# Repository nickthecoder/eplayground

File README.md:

Modular prototyping boards for Arduino and other microcontrollers.

[ePlayground Web Site](http://nickthecoder.co.uk/wiki/view/software/ePlayground)

I don't like using breadboards, so instead, I've created a set of modules which can be plugged together to
help prototype elecronics projects.

Simple projects can be created by just connecting various modules together, and adding a few jumpers.

The aim is to make electronics as easy as Lego, without loss of functionality.
These boards are for prototyping only, I don't expect to ever use them for a final product.

First choose a "Main" module, which houses your microprocessor. The Arduino Nana module is a good starting place.
Then plug in the modules required. All modules share a "standard" connector consisting of 8 data lines, plus VIN, VCC and GND.
Modules can be chained together, so if one module uses 3 pins, the other five pins can be used by other modules further down the chain.

I think this is a far better solution than the numerous "shields", because shields only work for a single platform.
An Arduino shield is no use with a WeMos or BluePill.
All modules lay flat. I think it is better than stacking modules, becuase a stack is useless if you want an LED screen on one, and buttons on another (which do you hide ;-)

Each board should do one thing well, and no more. So for example, the main modules don't have LEDs, buttons, header pins etc. If you want those, plug in the appropriate module.

Most modules are 5x5 cm, but some double-size, and others half-size.

Modules plug together using right angled header pins. This is cheap and simple, but they aren't designed for this,
and care is needed when soldering to ensure the boards line up nicely.
The female socket needs to be lifted slightly, so the the pins only just produde through the circuit board.

## Main Modules

* Diyduino (A DIP-28 AT Mega 328 chip, plus crystal + caps etc)
* Pro-Mini
* Nano
* BluePill
* WeMos - Can also be connected to another "Main" module, and communicate via serial lines (TXD, RXD).

These all have a "standard" connector consisting of 8 data lines, plus VIN, VCC and GND.
The Arduino modules have 3 such connectors, the BluePill has 4, and WeMos just 1.

## Regular Modules

* Triple Headers - a half size module with GND, VCC and data for each of the eight lines.
* LED - Shows the status of each of the lines using an LED.
* Buttons - Simple push buttons.
* Pots - Four potentiometers (must be connected to the Analog connection)
* IO Expander. Uses a 23017 chip to give an aditional 16 pins.
* Shift-595 - Adds 16 output lines using two 595 shift registers. Can be chained to give as many outputs as needed).
* Level Converter - A bi-directional conversion from 5V to 3.3V.
* MAX7219 - Drives a LEDs in an 8x6 array, plus upto 16 buttons. via I2C.
* Multiplexer - Multiplexes 8 analog inputs onto a signal pin. Can be chained for upto 40 inputs. Can also be used for digital signals.
* Power - Pwers the VIN line from a barrel jack (or screw terminals).
* Prototype - A blank board with an array of holes to solder whatever you like.
* StripLED - Control RGB LED strips (both common anode and common cathode).

Note, the outputs from the Multiplexer, IO Expander and Shift-595 use the same standard connector.
So, for example, if you need 32 buttons, then use 2 IO Expanders, and connect 2 button modules to each.
It will take less than a minute to connect!

Most of these boards haven't been tested yet, so use at your own risk!

## Software

The modules can be used directly without any specific software, however, I also have an Arduino library which helps
drive these modules called [AbstractIO](https://github.com/nickthecoder/abstractIO).

The examples in the AbstractIO library are designed to be simple to set up with eplayground modules,
e.g. pin numbers are chosen, so that only jumpers are needed to "wire up" the the cicuits.
No actual wires required ;-)

All of my testing of the AbstractIO library was done using eplayground modules.

## Planned Modules

* Latched Inputs / Outputs. Use a pair of 8 bit latches to switch between two sets of inputs or outputs.
If I use a bi-directional latch, one board can be configured for either input or output.
* External PWM chip (useful for microcontrollers with few PWM pins of their own).
* PIC based "main" module. Allow the PIC to be used as a "Main" module, but also as a regular module e.g. to talk to an Arduino via I2c.
* Motor driver and/or stepper motor driver.
* Real time clock - I'll probably just solder this to a "prototype" module.
* IR LED and Sensor (for remote controls). Probably a job for the "prototype" module rather than a custom board.
* Rasberry Pi (Just a IDC ribbon cable to the PI, plus the usual connectors).
I've read that max current is low, and are not as forgiving to high currents, so maybe some extra protection should be included.

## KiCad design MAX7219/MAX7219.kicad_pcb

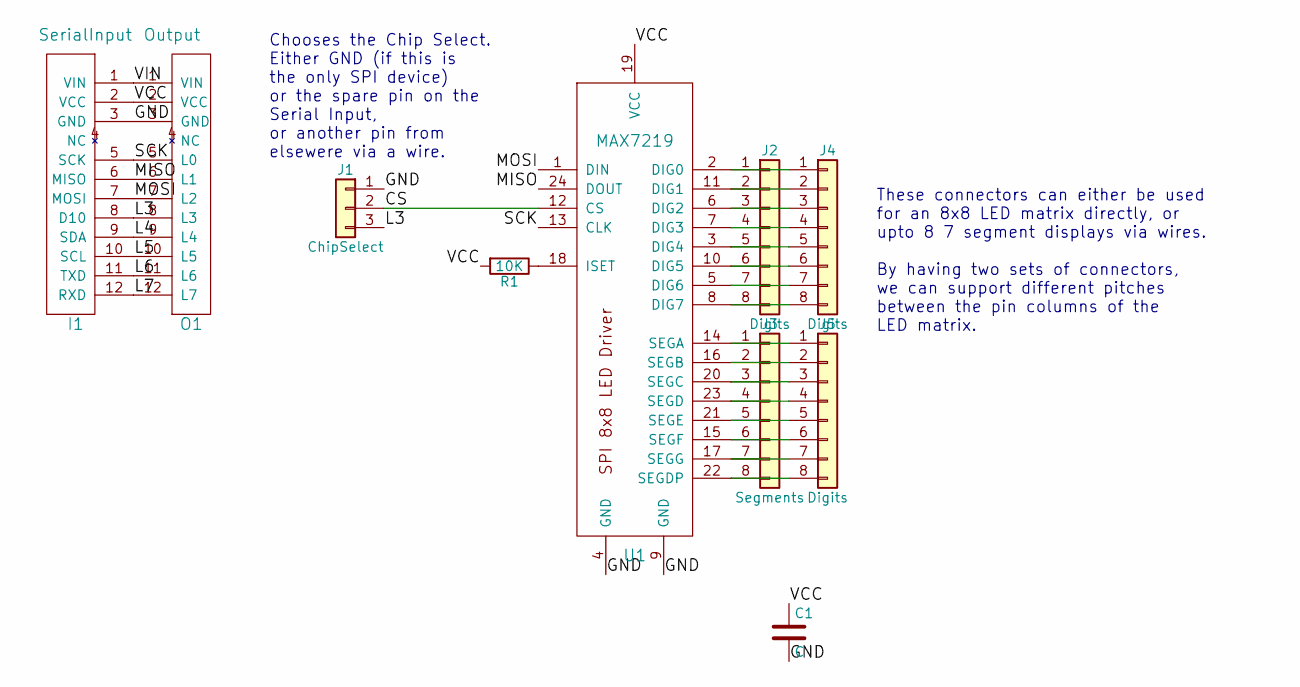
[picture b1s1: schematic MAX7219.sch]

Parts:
C1: C; C_Disc_D3.8mm_W2.6mm_P2.50mm
I1: SerialInput; Pin_Header_Straight_1x12_Pitch2.54mm
J1: ChipSelect; Pin_Header_Straight_1x03_Pitch2.54mm
J2, J4, J5: Digits; Pin_Header_Straight_1x08_Pitch2.54mm
J3: Segments; Pin_Header_Straight_1x08_Pitch2.54mm
O1: Output; Pin_Header_Straight_1x12_Pitch2.54mm
R1: 10K; R_Axial_DIN0204_L3.6mm_D1.6mm_P7.62mm_Horizontal
U1: MAX7219; DIP-24_W7.62mm

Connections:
/CS: J1.2, U1.12 (CS)
/GND: C1.2, I1.3 (GND), J1.1, O1.3 (GND), U1.4 (GND), U1.9 (GND)
/L3: I1.8 (D10), J1.3, O1.8 (L3)
/L4: I1.9 (SDA), O1.9 (L4)
/L5: I1.10 (SCL), O1.10 (L5)
/L6: I1.11 (TXD), O1.11 (L6)
/L7: I1.12 (RXD), O1.12 (L7)
/MISO: I1.6 (MISO), O1.6 (L1), U1.24 (DOUT)
/MOSI: I1.7 (MOSI), O1.7 (L2), U1.1 (DIN)
/SCK: I1.5 (SCK), O1.5 (L0), U1.13 (CLK)
/VCC: C1.1, I1.2 (VCC), O1.2 (VCC), R1.2, U1.19 (VCC)
/VIN: I1.1 (VIN), O1.1 (VIN)
unnamed: J2.1, J4.1, U1.2 (DIG0)
unnamed: J2.2, J4.2, U1.11 (DIG1)
unnamed: J2.3, J4.3, U1.6 (DIG2)
unnamed: J2.4, J4.4, U1.7 (DIG3)
unnamed: J2.5, J4.5, U1.3 (DIG4)
unnamed: J2.6, J4.6, U1.10 (DIG5)
unnamed: J2.7, J4.7, U1.5 (DIG6)
unnamed: J2.8, J4.8, U1.8 (DIG7)
unnamed: J3.1, J5.1, U1.14 (SEGA)
unnamed: J3.2, J5.2, U1.16 (SEGB)
unnamed: J3.3, J5.3, U1.20 (SEGC)
unnamed: J3.4, J5.4, U1.23 (SEGD)
unnamed: J3.5, J5.5, U1.21 (SEGE)
unnamed: J3.6, J5.6, U1.15 (SEGF)
unnamed: J3.7, J5.7, U1.17 (SEGG)
unnamed: J3.8, J5.8, U1.22 (SEGDP)
unnamed: R1.1, U1.18 (ISET)

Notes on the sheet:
Chooses the Chip Select. Either GND (if this is the only SPI device) or the spare pin on the Serial Input, or another pin from elsewere via a wire.
These connectors can either be used for an 8x8 LED matrix directly, or upto 8 7 segment displays via wires. By having two sets of connectors, we can support different pitches between the pin columns of the LED matrix.

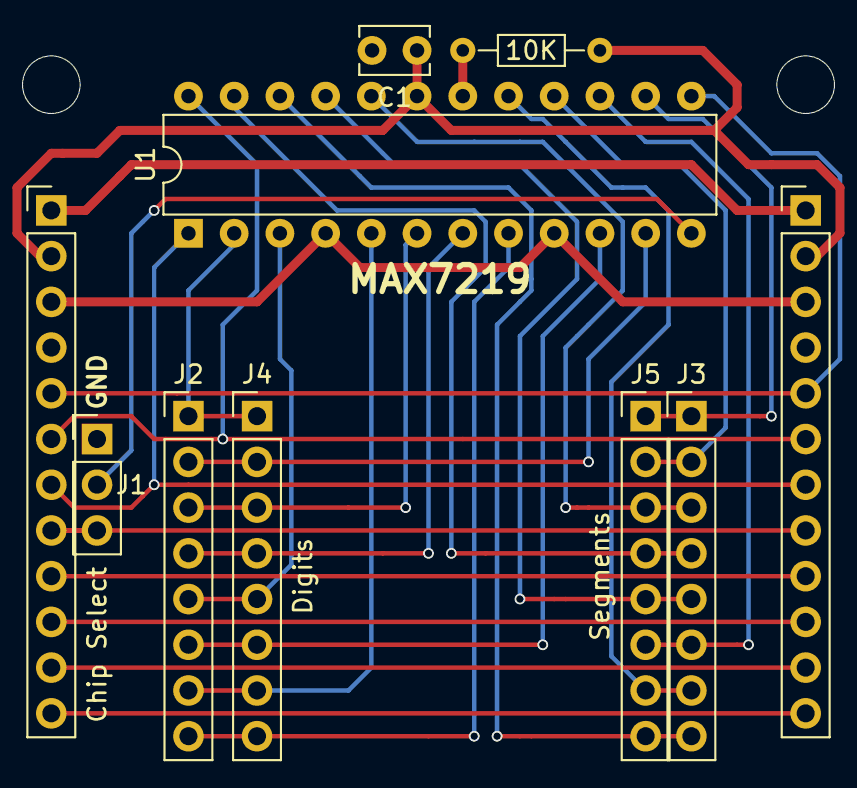
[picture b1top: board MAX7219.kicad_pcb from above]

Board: 2 copper layers, 12 parts (0 on the bottom side), 29 nets.

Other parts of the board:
M3, M3#2: MountingHole_3.2mm_M3

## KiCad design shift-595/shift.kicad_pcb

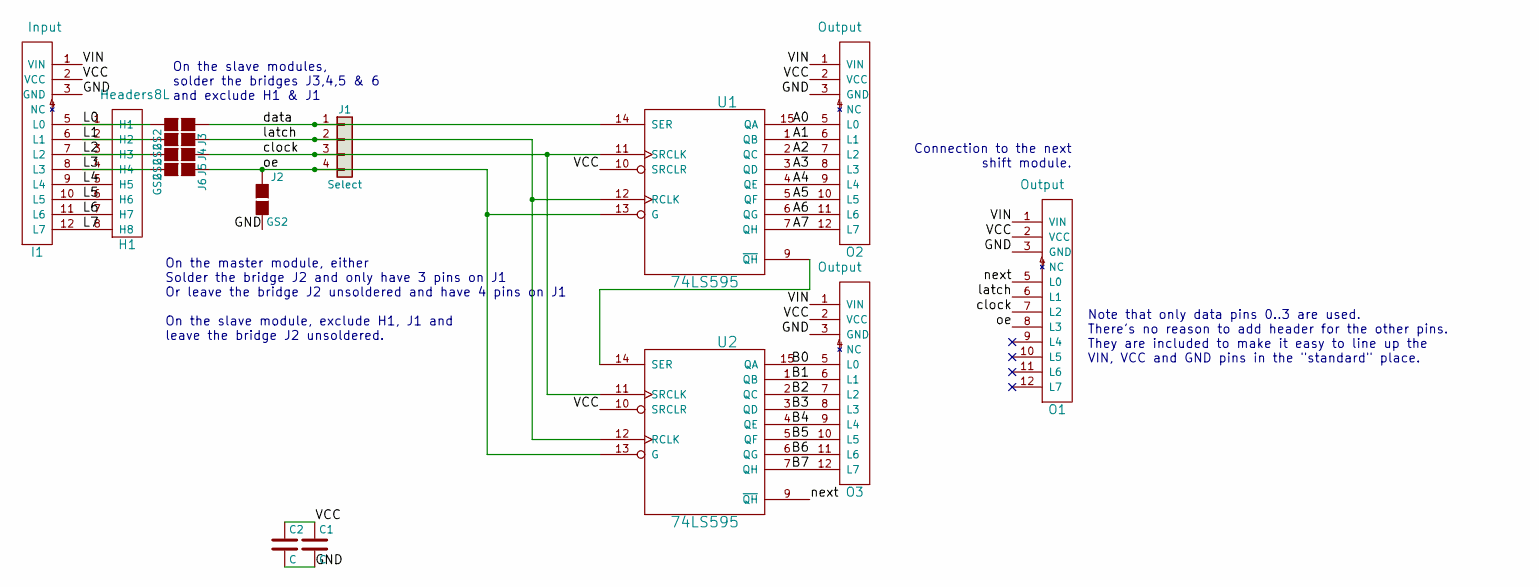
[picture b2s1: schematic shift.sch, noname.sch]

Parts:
C1, C2: C; C_Disc_D3.0mm_W2.0mm_P2.50mm
H1: Headers8L; Pin_Header_Straight_1x08_Pitch2.54mm
I1: Input; Pin_Header_Straight_1x12_Pitch2.54mm
J1: Select; Pin_Header_Straight_1x04_Pitch2.54mm
J2, J3, J4, J5, J6: GS2
O1, O2, O3: Output; Socket_Strip_Straight_1x12_Pitch2.54mm
U1, U2: 74LS595; DIP-16_W7.62mm

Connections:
/A0: O2.5 (L0), U1.15 (QA)
/A1: O2.6 (L1), U1.1 (QB)
/A2: O2.7 (L2), U1.2 (QC)
/A3: O2.8 (L3), U1.3 (QD)
/A4: O2.9 (L4), U1.4 (QE)
/A5: O2.10 (L5), U1.5 (QF)
/A6: O2.11 (L6), U1.6 (QG)
/A7: O2.12 (L7), U1.7 (QH)
/B0: O3.5 (L0), U2.15 (QA)
/B1: O3.6 (L1), U2.1 (QB)
/B2: O3.7 (L2), U2.2 (QC)
/B3: O3.8 (L3), U2.3 (QD)
/B4: O3.9 (L4), U2.4 (QE)
/B5: O3.10 (L5), U2.5 (QF)
/B6: O3.11 (L6), U2.6 (QG)
/B7: O3.12 (L7), U2.7 (QH)
/L0: H1.1 (H1), I1.5 (L0), J3.2 (G2)
/L1: H1.2 (H2), I1.6 (L1), J4.2 (G2)
/L2: H1.3 (H3), I1.7 (L2), J5.2 (G2)
/L3: H1.4 (H4), I1.8 (L3), J6.2 (G2)
/L4: H1.5 (H5), I1.9 (L4)
/L5: H1.6 (H6), I1.10 (L5)
/L6: H1.7 (H7), I1.11 (L6)
/L7: H1.8 (H8), I1.12 (L7)
/VIN: I1.1 (VIN), O1.1 (VIN), O2.1 (VIN), O3.1 (VIN)
/clock: J1.3, J5.1 (G1), O1.7 (L2), U1.11 (SRCLK), U2.11 (SRCLK)
/data: J1.1, J3.1 (G1), U1.14 (SER)
/latch: J1.2, J4.1 (G1), O1.6 (L1), U1.12 (RCLK), U2.12 (RCLK)
/next: O1.5 (L0), U2.9 (~QH)
/oe: J1.4, J2.1 (G1), J6.1 (G1), O1.8 (L3), U1.13 (G), U2.13 (G)
GND: C1.2, C2.2, I1.3 (GND), J2.2 (G2), O1.3 (GND), O2.3 (GND), O3.3 (GND), U1.8 (GND), U2.8 (GND)
unnamed: U1.9 (~QH), U2.14 (SER)
VCC: C1.1, C2.1, I1.2 (VCC), O1.2 (VCC), O2.2 (VCC), O3.2 (VCC), U1.10 (SRCLR), U1.16 (VCC), U2.10 (SRCLR), U2.16 (VCC)

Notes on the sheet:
Connection to the next shift module.
Note that only data pins 0..3 are used. There's no reason to add header for the other pins. They are included to make it easy to line up the VIN, VCC and GND pins in the "standard" place.
On the master module, either Solder the bridge J2 and only have 3 pins on J1 Or leave the bridge J2 unsoldered and have 4 pins on J1 On the slave module, exclude H1, J1 and leave the bridge J2 unsoldered.
On the slave modules, solder the bridges J3,4,5 & 6 and exclude H1 & J1

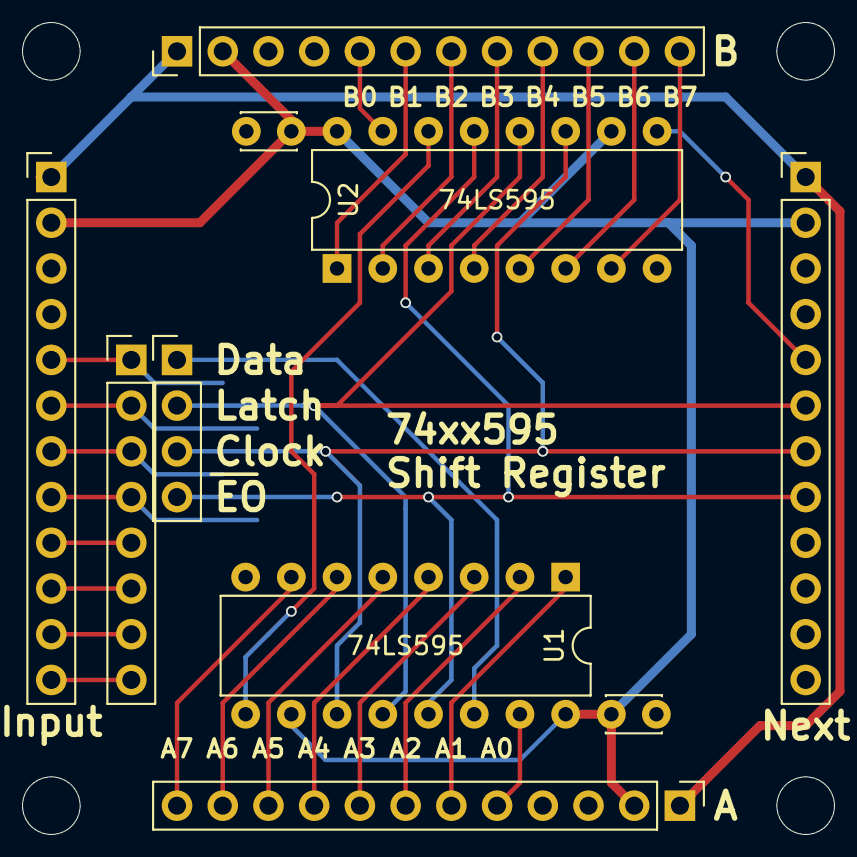
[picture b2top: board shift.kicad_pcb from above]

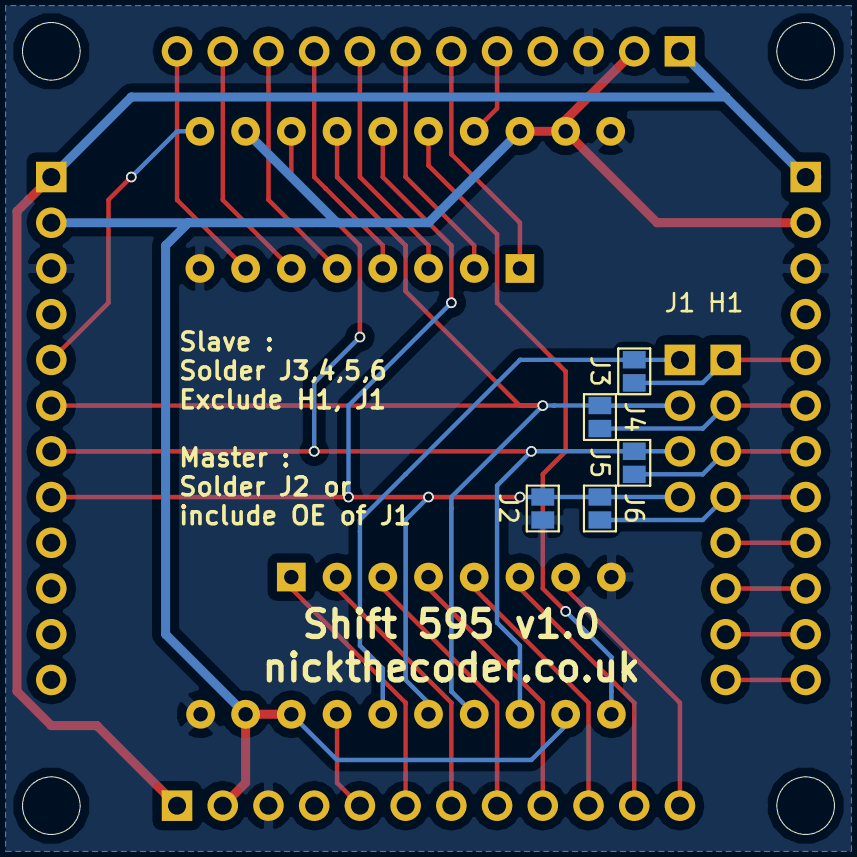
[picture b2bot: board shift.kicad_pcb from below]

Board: 2 copper layers, 17 parts (5 on the bottom side), 33 nets.

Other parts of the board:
M3, M3#2: MountingHole_3.2mm_M3

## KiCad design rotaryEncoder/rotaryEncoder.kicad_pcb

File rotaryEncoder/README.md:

Rotary Encoder
==============

Houses two rotary encoders, with a push button.

There are 6 pull-up resistors.

Add jumpers to enable each encoder.

## Version History

## Version 1.0

Works fine (though I haven't used the push buttons yet).

## Version 1.1

Consider moving the encoders to the right slightly, leaving more space for the jumpers.

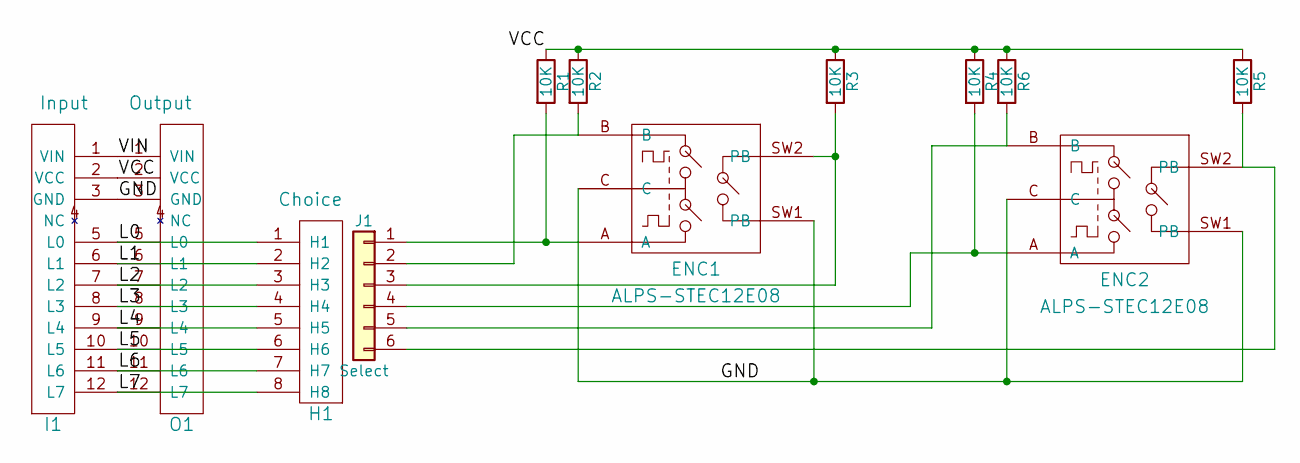
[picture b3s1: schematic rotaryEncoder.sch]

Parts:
ENC1, ENC2: ALPS-STEC12E08; ALPS_STEC12E08
H1: Choice; Pin_Header_Straight_1x08_Pitch2.54mm
I1: Input; Pin_Header_Straight_1x12_Pitch2.54mm
J1: Select; Pin_Header_Straight_1x06_Pitch2.54mm
O1: Output; Socket_Strip_Straight_1x12_Pitch2.54mm
R1, R2, R3, R4, R5, R6: 10K; R_Axial_DIN0204_L3.6mm_D1.6mm_P7.62mm_Horizontal

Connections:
/GND: ENC1.C, ENC1.SW1 (PB), ENC2.C, ENC2.SW1 (PB), I1.3 (GND), O1.3 (GND)
/L0: H1.1 (H1), I1.5 (L0), O1.5 (L0)
/L1: H1.2 (H2), I1.6 (L1), O1.6 (L1)
/L2: H1.3 (H3), I1.7 (L2), O1.7 (L2)
/L3: H1.4 (H4), I1.8 (L3), O1.8 (L3)
/L4: H1.5 (H5), I1.9 (L4), O1.9 (L4)
/L5: H1.6 (H6), I1.10 (L5), O1.10 (L5)
/L6: H1.7 (H7), I1.11 (L6), O1.11 (L6)
/L7: H1.8 (H8), I1.12 (L7), O1.12 (L7)
/VCC: I1.2 (VCC), O1.2 (VCC), R1.1, R2.1, R3.1, R4.1, R5.1, R6.1
/VIN: I1.1 (VIN), O1.1 (VIN)
unnamed: ENC1.A, J1.1, R1.2
unnamed: ENC1.B, J1.2, R2.2
unnamed: ENC1.SW2 (PB), J1.3, R3.2
unnamed: ENC2.A, J1.4, R4.2
unnamed: ENC2.B, J1.5, R6.2
unnamed: ENC2.SW2 (PB), J1.6, R5.2

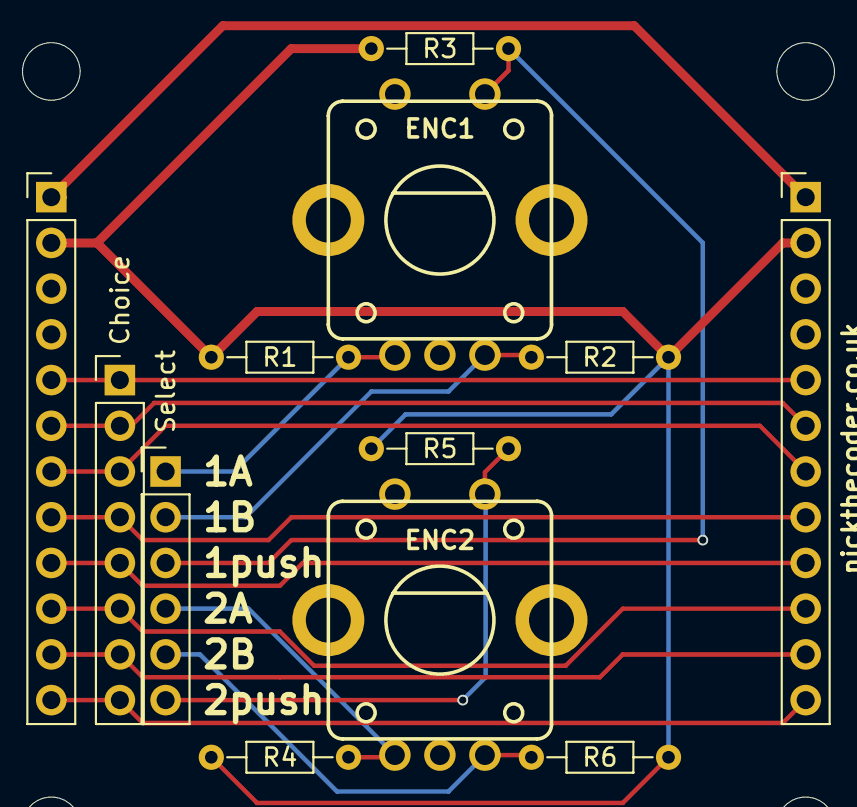
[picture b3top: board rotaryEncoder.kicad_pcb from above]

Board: 2 copper layers, 14 parts (0 on the bottom side), 17 nets.

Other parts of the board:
M3, M3#2: MountingHole_3.2mm_M3

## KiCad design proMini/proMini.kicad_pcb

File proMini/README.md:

Pro Mini
========

A simple module, with a socket for an Arduino Pro Mini.

There's no standard layout for Pro-Minis. Clones place the A6 and A7 in different places.
This module supports two common versions, but I have seen other versions which are slightly incompatible.
(I can't support this third version on the same PCB, as the pins are half-pitch from other versions).

There are three standard connectors, in the same configuration as the Nano and DIYDuino modules.

## Notes

Powered from from USB via the ICSP connector only.

## Soldering Notes

There are two ICSP headers, with the TX and RX reversed.
You can of course ignore both of these, and use the one on the Pro-Mini itself.

The lables of TX and RX can be confusing, because they depend on your point of view.
(A receive is somebody else's transmit!). These are labelled from the AT Mega's point of view.

## Version History

### Version 1.0

At time of writing I haven't tested this module.

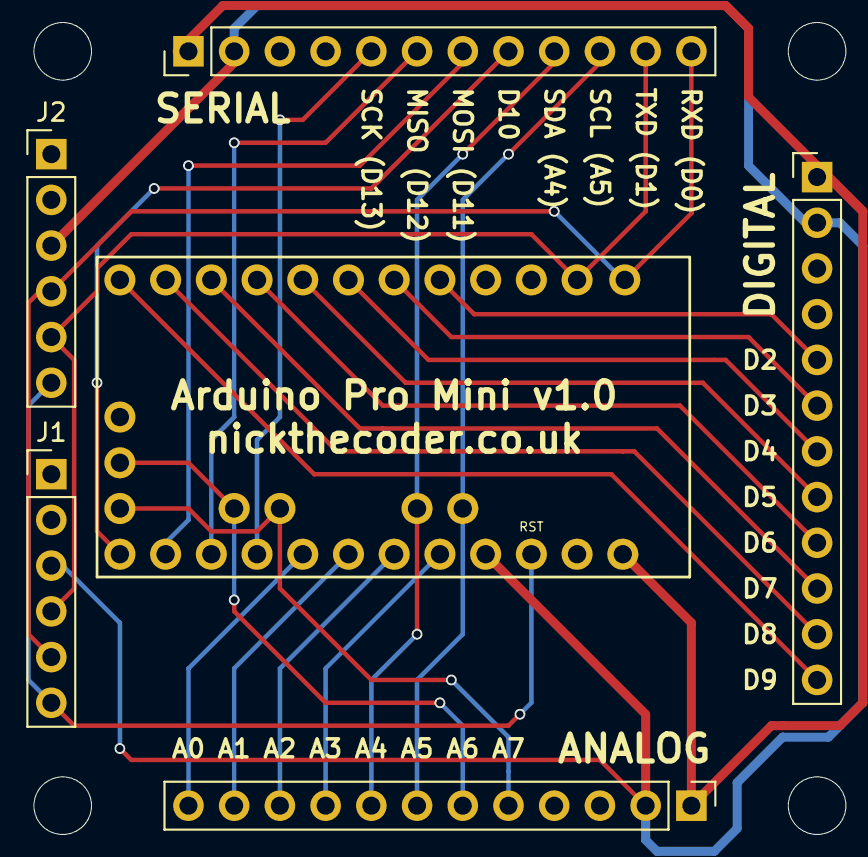
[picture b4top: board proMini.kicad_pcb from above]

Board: 2 copper layers, 8 parts (0 on the bottom side), 26 nets.

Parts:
J1, J2: ICSP; Pin_Header_Straight_1x06_Pitch2.54mm
O1: SerialOutput; Socket_Strip_Straight_1x12_Pitch2.54mm
O2, O3: Output; Socket_Strip_Straight_1x12_Pitch2.54mm
X: M3; MountingHole_3.2mm_M3
X#2: M3; MountingHole_3.2mm_M3
XA1: Arduino_Mini_01_Socket; Arduino_ProMini_NoICSP

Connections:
/A0: O3.12, XA1.A0
/A1: O3.11, XA1.A1
/A2: O3.10, XA1.A2
/A3: O3.9, XA1.A3
/A4: O1.9, O3.8, XA1.A4
/A5: O1.10, O3.7, XA1.A5
/A6: O3.6, XA1.A6
/A7: O3.5, XA1.A7
/D0: J1.5, J2.4, O1.12, XA1.D0
/D1: J1.4, J2.5, O1.11, XA1.D1
/D2: O2.5, XA1.D2
/D3: O2.6, XA1.D3
/D4: O2.7, XA1.D4
/D5: O2.8, XA1.D5
/D6: O2.9, XA1.D6
/D7: O2.10, XA1.D7
/D8: O2.11, XA1.D8
/D9: O2.12, XA1.D9
/D10: O1.8, XA1.D10
/D11: O1.7, XA1.D11
/D12: O1.6, XA1.D12
/D13: O1.5, XA1.D13
/GND: J1.1, J1.2, J2.1, J2.2, O1.3, O2.3, O3.3, XA1.GND2, XA1.GND4
/RESET: J1.6, J2.6, XA1.RST2
/VCC: J1.3, J2.3, O1.2, O2.2, O3.2, XA1.5V1
/VIN: O1.1, O2.1, O3.1, XA1.VIN

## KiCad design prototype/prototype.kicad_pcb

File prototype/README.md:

Prototype
=========

I plan to use these to create one-off custom modules.
For example, I'll use one for an I2C real-time clock.

The long rows near the top are power rails VIN, VCC and GND.

The left-most column is connected to the input's data lines.

The right-most column is connected to the output's data lines.
If the solder bridges are soldered, then the outputs will be the same as the inputs.

The top and bottom of the board have options for additional standard connectors.

The remaining pads are unconnected.

## Soldering Notes

There are solder bridges on the back, which allow the data pins to pass through to the opposite side.
Unless you use the opposite side for something else, I recommend soldering these bridges.

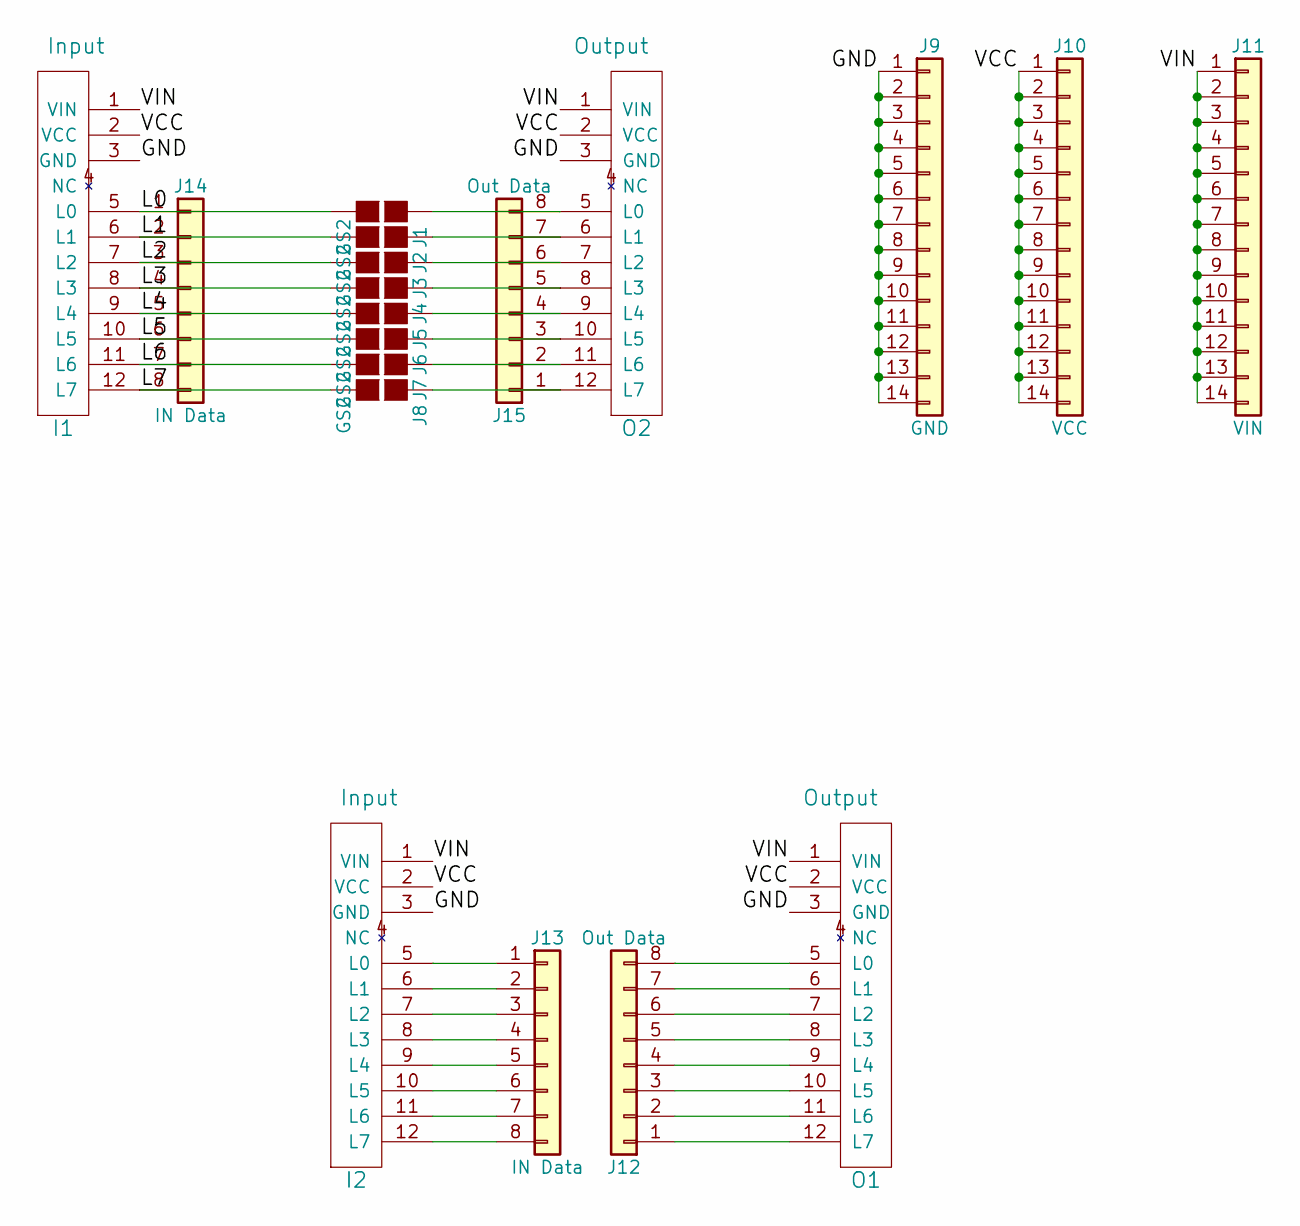
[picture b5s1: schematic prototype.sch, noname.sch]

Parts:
I1, I2: Input; Pin_Header_Straight_1x12_Pitch2.54mm
J1, J2, J3, J4, J5, J6, J7, J8: GS2
J9: GND; Pin_Header_Straight_1x14_Pitch2.54mm
J10: VCC; Pin_Header_Straight_1x14_Pitch2.54mm
J11: VIN; Pin_Header_Straight_1x14_Pitch2.54mm
J12, J15: Out Data; Pin_Header_Straight_1x08_Pitch2.54mm
J13, J14: IN Data; Pin_Header_Straight_1x08_Pitch2.54mm
O1, O2: Output; Socket_Strip_Straight_1x12_Pitch2.54mm

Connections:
/GND: I1.3 (GND), I2.3 (GND), J9.1, J9.2, J9.3, J9.4, J9.5, J9.6, J9.7, J9.8, J9.9, J9.10, J9.11, J9.12, J9.13, J9.14, O1.3 (GND), O2.3 (GND)
/L0: I1.5 (L0), J1.2 (G2), J14.1
/L1: I1.6 (L1), J2.2 (G2), J14.2
/L2: I1.7 (L2), J3.2 (G2), J14.3
/L3: I1.8 (L3), J4.2 (G2), J14.4
/L4: I1.9 (L4), J5.2 (G2), J14.5
/L5: I1.10 (L5), J6.2 (G2), J14.6
/L6: I1.11 (L6), J7.2 (G2), J14.7
/L7: I1.12 (L7), J8.2 (G2), J14.8
/VCC: I1.2 (VCC), I2.2 (VCC), J10.1, J10.2, J10.3, J10.4, J10.5, J10.6, J10.7, J10.8, J10.9, J10.10, J10.11, J10.12, J10.13, J10.14, O1.2 (VCC), O2.2 (VCC)
/VIN: I1.1 (VIN), I2.1 (VIN), J11.1, J11.2, J11.3, J11.4, J11.5, J11.6, J11.7, J11.8, J11.9, J11.10, J11.11, J11.12, J11.13, J11.14, O1.1 (VIN), O2.1 (VIN)
unnamed: I2.5 (L0), J13.1
unnamed: I2.6 (L1), J13.2
unnamed: I2.7 (L2), J13.3
unnamed: I2.8 (L3), J13.4
unnamed: I2.9 (L4), J13.5
unnamed: I2.10 (L5), J13.6
unnamed: I2.11 (L6), J13.7
unnamed: I2.12 (L7), J13.8
unnamed: J1.1 (G1), J15.8, O2.5 (L0)
unnamed: J12.1, O1.12 (L7)
unnamed: J12.2, O1.11 (L6)
unnamed: J12.3, O1.10 (L5)
unnamed: J12.4, O1.9 (L4)
unnamed: J12.5, O1.8 (L3)
unnamed: J12.6, O1.7 (L2)
unnamed: J12.7, O1.6 (L1)
unnamed: J12.8, O1.5 (L0)
unnamed: J8.1 (G1), J15.1, O2.12 (L7)
unnamed: J7.1 (G1), J15.2, O2.11 (L6)
unnamed: J6.1 (G1), J15.3, O2.10 (L5)
unnamed: J5.1 (G1), J15.4, O2.9 (L4)
unnamed: J4.1 (G1), J15.5, O2.8 (L3)
unnamed: J3.1 (G1), J15.6, O2.7 (L2)
unnamed: J2.1 (G1), J15.7, O2.6 (L1)

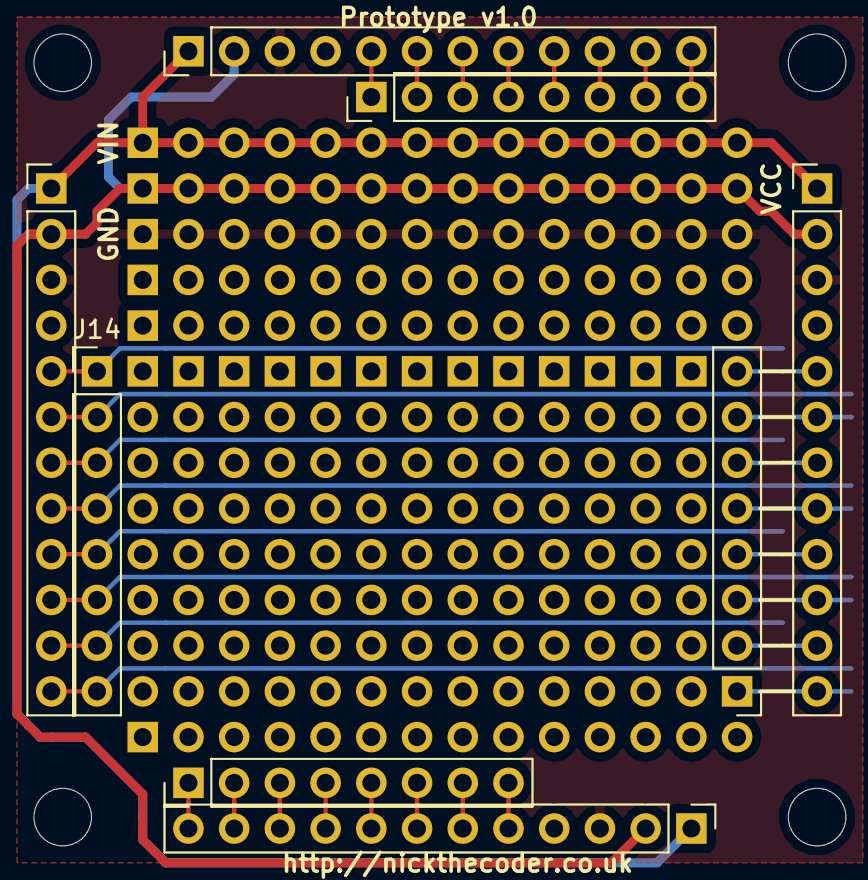
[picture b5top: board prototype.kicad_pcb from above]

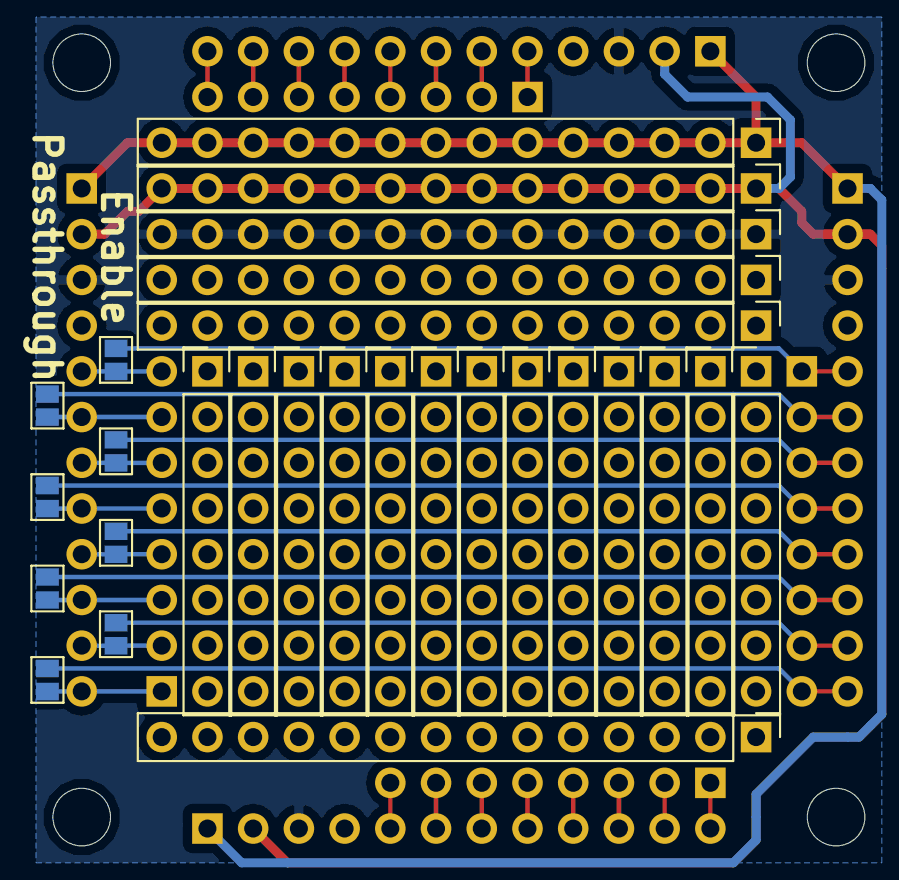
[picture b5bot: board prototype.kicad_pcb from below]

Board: 2 copper layers, 21 parts (11 on the bottom side), 35 nets.

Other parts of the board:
M3, M3#2: MountingHole_3.2mm_M3

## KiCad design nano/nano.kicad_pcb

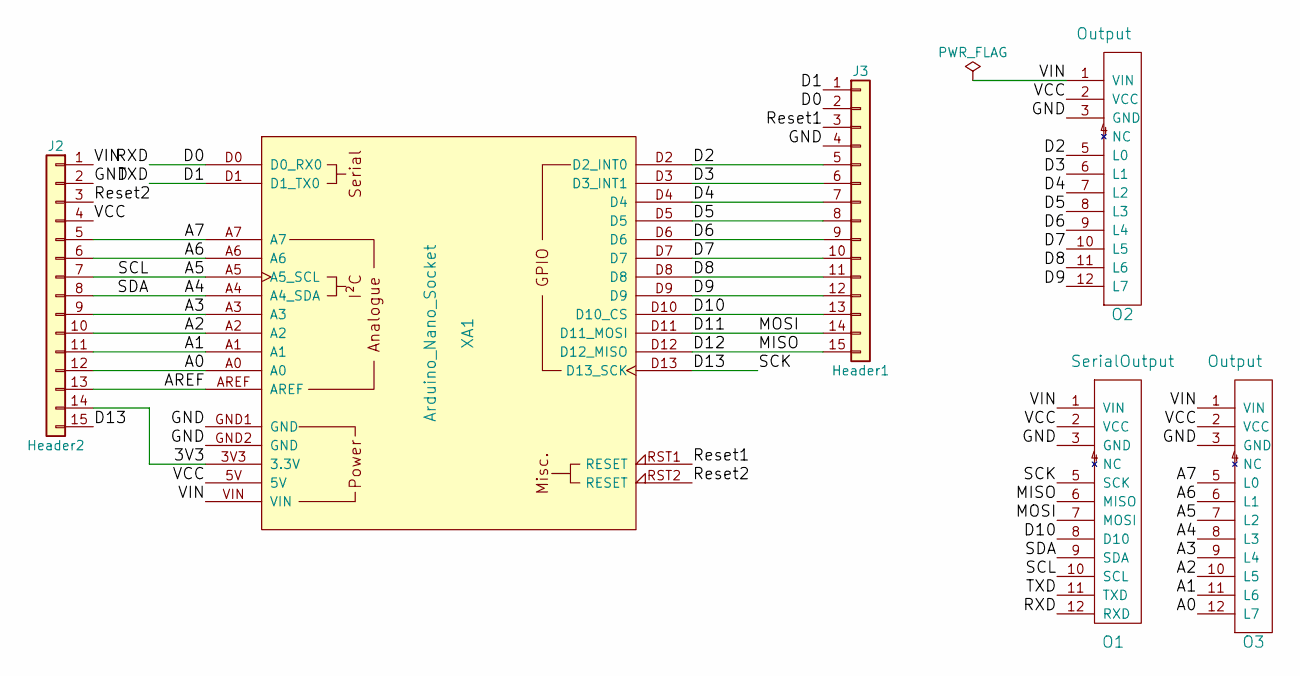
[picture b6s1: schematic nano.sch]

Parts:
J2: Header2; Pin_Header_Straight_1x15_Pitch2.54mm
J3: Header1; Pin_Header_Straight_1x15_Pitch2.54mm
O1: SerialOutput; Socket_Strip_Straight_1x12_Pitch2.54mm
O2, O3: Output; Socket_Strip_Straight_1x12_Pitch2.54mm
XA1: Arduino_Nano_Socket; Arduino_Nano

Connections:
/3V3: J2.14, XA1.3V3 (3.3V)
/A0: J2.12, O3.12 (L7), XA1.A0
/A1: J2.11, O3.11 (L6), XA1.A1
/A2: J2.10, O3.10 (L5), XA1.A2
/A3: J2.9, O3.9 (L4), XA1.A3
/A4: J2.8, O1.9 (SDA), O3.8 (L3), XA1.A4 (A4_SDA)
/A5: J2.7, O1.10 (SCL), O3.7 (L2), XA1.A5 (A5_SCL)
/A6: J2.6, O3.6 (L1), XA1.A6
/A7: J2.5, O3.5 (L0), XA1.A7
/AREF: J2.13, XA1.AREF
/D0: J3.2, O1.12 (RXD), XA1.D0 (D0_RX0)
/D1: J3.1, O1.11 (TXD), XA1.D1 (D1_TX0)
/D2: J3.5, O2.5 (L0), XA1.D2 (D2_INT0)
/D3: J3.6, O2.6 (L1), XA1.D3 (D3_INT1)
/D4: J3.7, O2.7 (L2), XA1.D4
/D5: J3.8, O2.8 (L3), XA1.D5
/D6: J3.9, O2.9 (L4), XA1.D6
/D7: J3.10, O2.10 (L5), XA1.D7
/D8: J3.11, O2.11 (L6), XA1.D8
/D9: J3.12, O2.12 (L7), XA1.D9
/D10: J3.13, O1.8 (D10), XA1.D10 (D10_CS)
/D11: J3.14, O1.7 (MOSI), XA1.D11 (D11_MOSI)
/D12: J3.15, O1.6 (MISO), XA1.D12 (D12_MISO)
/D13: J2.15, O1.5 (SCK), XA1.D13 (D13_SCK)
/GND: J2.2, J3.4, O1.3 (GND), O2.3 (GND), O3.3 (GND), XA1.GND1 (GND), XA1.GND2 (GND)
/Reset1: J3.3, XA1.RST1 (RESET)
/Reset2: J2.3, XA1.RST2 (RESET)
/VCC: J2.4, O1.2 (VCC), O2.2 (VCC), O3.2 (VCC), XA1.5V
/VIN: J2.1, O1.1 (VIN), O2.1 (VIN), O3.1 (VIN), XA1.VIN

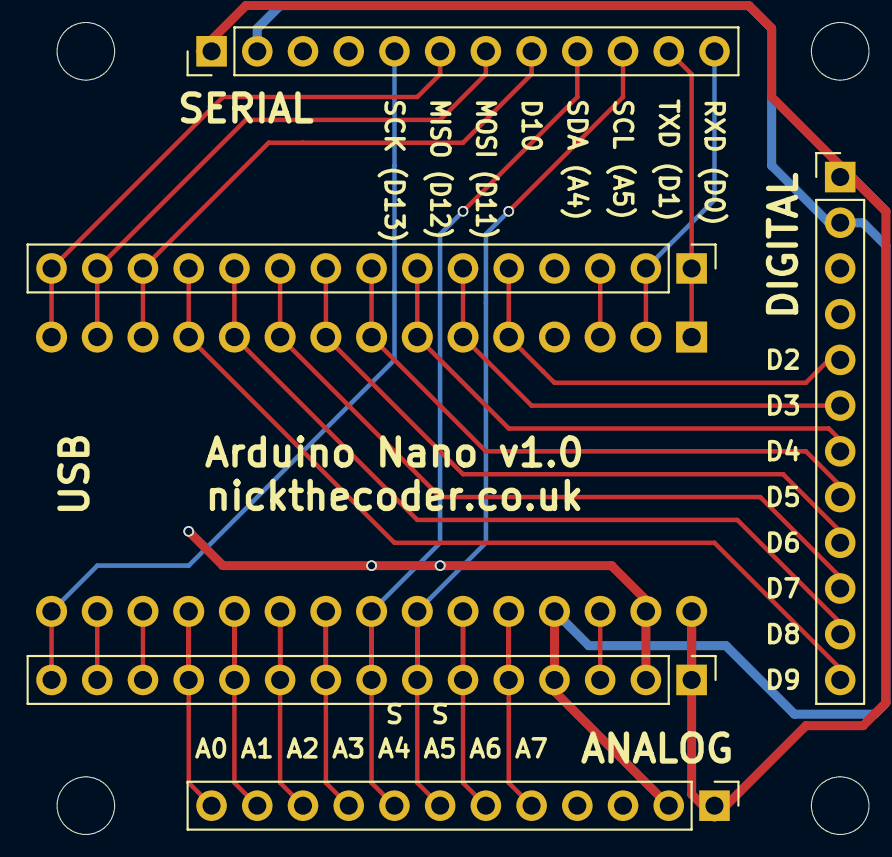
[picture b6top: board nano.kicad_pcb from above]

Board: 2 copper layers, 8 parts (0 on the bottom side), 29 nets.

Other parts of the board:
X: M3; MountingHole_3.2mm_M3
X#2: M3; MountingHole_3.2mm_M3

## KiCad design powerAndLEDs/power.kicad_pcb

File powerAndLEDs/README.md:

Power
=====

A half-sized module to connect power via a DC Barrel Jack or screw terminals to the VIN pin of the standard connector.

I use this in conjunction with the Strip LED modules to power strips of LEDs.

LEDs
====

A half-sized module which is simply a bank of LEDs for each pin.

Use jumpers links between H1 and H2 to enable each of the LEDs.

## Soldering Notes

**Power Module**

Check the orientation of the toggle switch SW1.

**LED module**

The module can be configured in two ways.
With the solder bridge to GND, the LEDs work as normal.

With the solder bridge to VCC, the LEDs work in reverse, i.e. **on** when the signal is **low** and **off** when it is **high**.
The polarity of the LEDs must be reversed.

Don't use the minimum value resistor, there really is no point having ultra bright indicators.
For a 5V VCC, I find 1K resistors are fine. This is probably too high for a 3.3V VCC though.

I chose rectangular LEDs for compactness. However, mine have a small lip at their base, which makes them slightly too large,
so I've had to remove the lips with cutters.

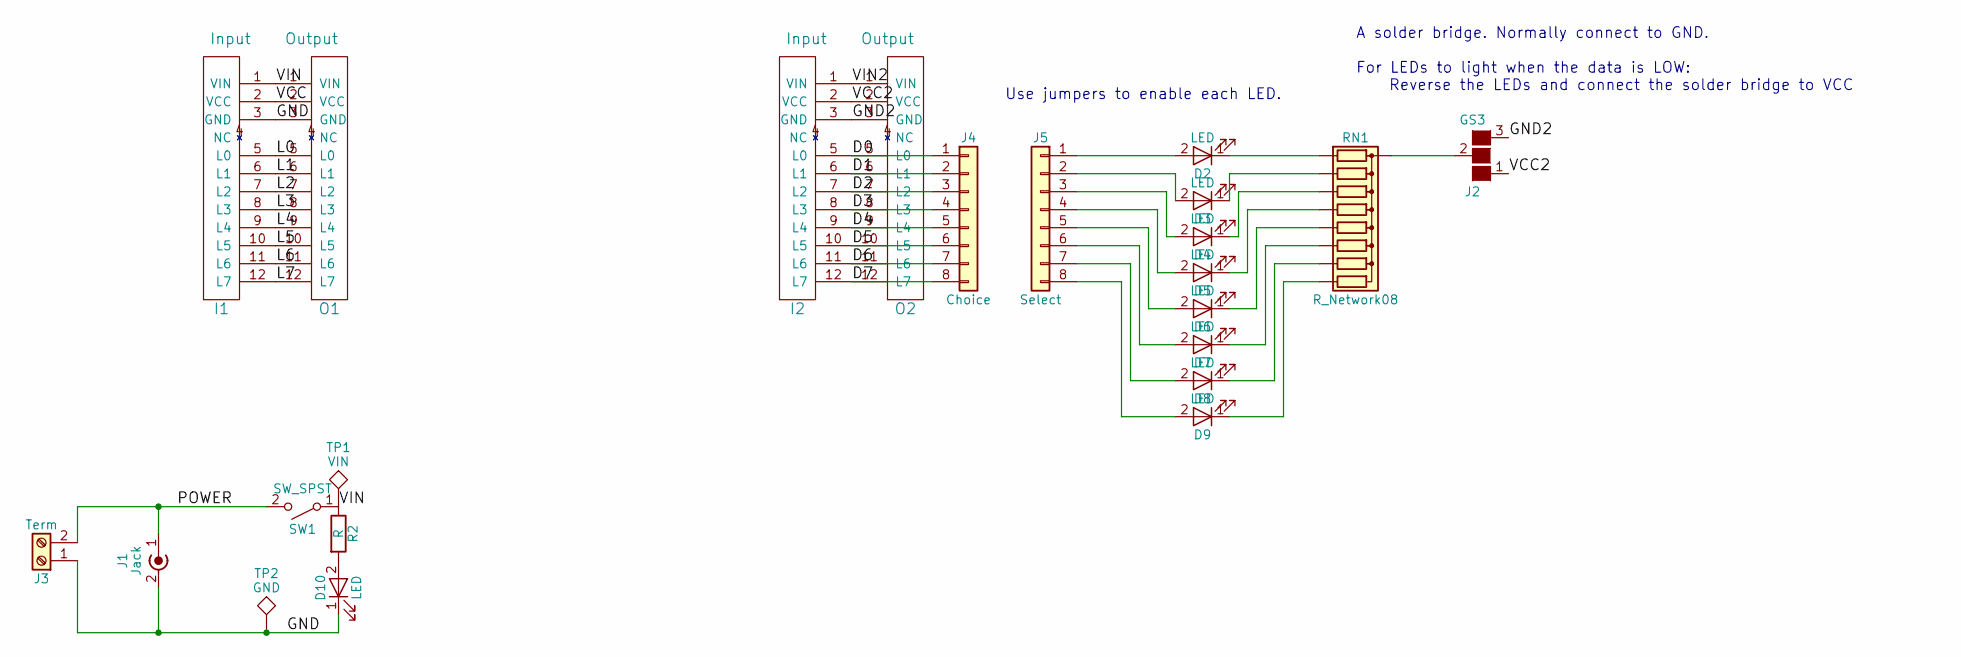
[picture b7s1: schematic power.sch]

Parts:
D2, D3, D4, D5, D6, D7, D8, D9: LED; LED_Rectangular_W3.0mm_H2.0mm
D10: LED; LED_D3.0mm
I1, I2: Input; Pin_Header_Straight_1x12_Pitch2.54mm
J1: Jack; BARREL_JACK
J2: GS3
J3: Term; TerminalBlock_Philmore_TB132_02x5mm_Straight
J4: Choice; Pin_Header_Straight_1x08_Pitch2.54mm
J5: Select; Pin_Header_Straight_1x08_Pitch2.54mm
O1, O2: Output; Socket_Strip_Straight_1x12_Pitch2.54mm
R2: R; R_Axial_DIN0204_L3.6mm_D1.6mm_P7.62mm_Horizontal
RN1: R_Network08; R_Array_SIP9
SW1: SW_SPST; SW_SPDT_8mm
TP1: VIN; PINTST
TP2: GND; PINTST

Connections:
/D0: I2.5 (L0), J4.1, O2.5 (L0)
/D1: I2.6 (L1), J4.2, O2.6 (L1)
/D2: I2.7 (L2), J4.3, O2.7 (L2)
/D3: I2.8 (L3), J4.4, O2.8 (L3)
/D4: I2.9 (L4), J4.5, O2.9 (L4)
/D5: I2.10 (L5), J4.6, O2.10 (L5)
/D6: I2.11 (L6), J4.7, O2.11 (L6)
/D7: I2.12 (L7), J4.8, O2.12 (L7)
/GND: D10.1 (K), I1.3 (GND), J1.2 (Ext), J3.1, O1.3 (GND), TP2.1
/GND2: I2.3 (GND), J2.3 (G3), O2.3 (GND)
/L0: I1.5 (L0), O1.5 (L0)
/L1: I1.6 (L1), O1.6 (L1)
/L2: I1.7 (L2), O1.7 (L2)
/L3: I1.8 (L3), O1.8 (L3)
/L4: I1.9 (L4), O1.9 (L4)
/L5: I1.10 (L5), O1.10 (L5)
/L6: I1.11 (L6), O1.11 (L6)
/L7: I1.12 (L7), O1.12 (L7)
/POWER: J1.1 (In), J3.2, SW1.2 (B)
/VCC: I1.2 (VCC), O1.2 (VCC)
/VCC2: I2.2 (VCC), J2.1 (G1), O2.2 (VCC)
/VIN: I1.1 (VIN), O1.1 (VIN), R2.1, SW1.1 (A), TP1.1
/VIN2: I2.1 (VIN), O2.1 (VIN)
unnamed: D2.1 (K), RN1.2 (R1)
unnamed: D2.2 (A), J5.1
unnamed: D3.1 (K), RN1.3 (R2)
unnamed: D3.2 (A), J5.2
unnamed: D4.1 (K), RN1.4 (R3)
unnamed: D4.2 (A), J5.3
unnamed: D5.1 (K), RN1.5 (R4)
unnamed: D5.2 (A), J5.4
unnamed: D6.1 (K), RN1.6 (R5)
unnamed: D6.2 (A), J5.5
unnamed: D7.1 (K), RN1.7 (R6)
unnamed: D7.2 (A), J5.6
unnamed: D8.1 (K), RN1.8 (R7)
unnamed: D8.2 (A), J5.7
unnamed: D9.1 (K), RN1.9 (R8)
unnamed: D9.2 (A), J5.8
unnamed: D10.2 (A), R2.2
unnamed: J2.2 (G2), RN1.1 (common)

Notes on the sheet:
A solder bridge. Normally connect to GND. For LEDs to light when the data is LOW: Reverse the LEDs and connect the solder bridge to VCC
Use jumpers to enable each LED.

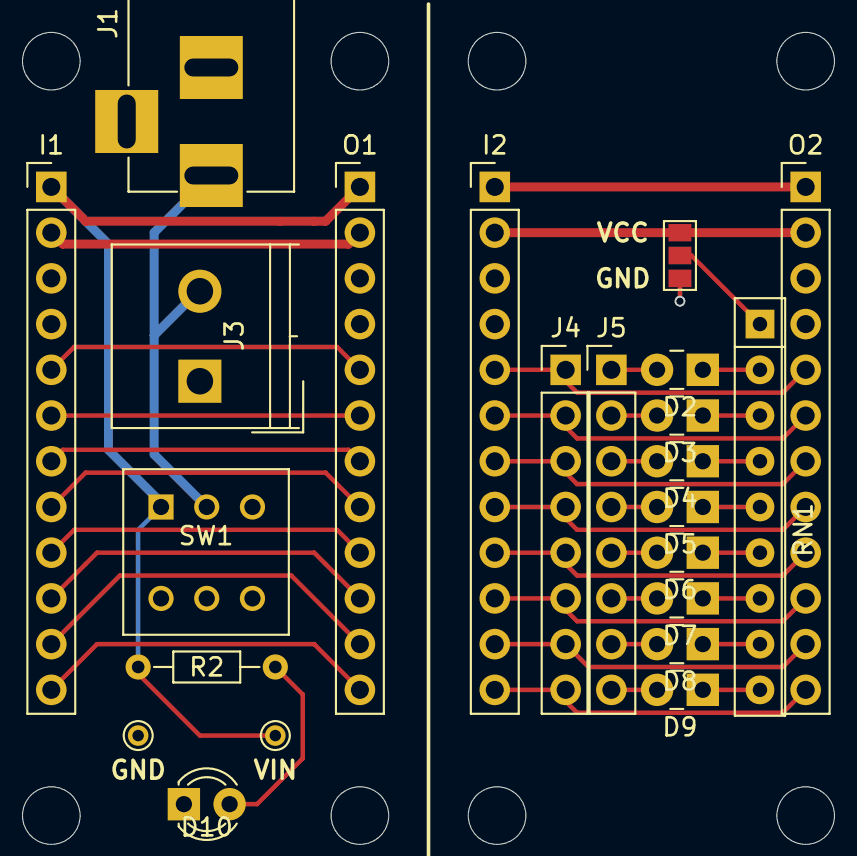
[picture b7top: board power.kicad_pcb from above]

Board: 2 copper layers, 25 parts (0 on the bottom side), 41 nets.

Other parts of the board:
M3, M3#2: MountingHole_3.2mm_M3
